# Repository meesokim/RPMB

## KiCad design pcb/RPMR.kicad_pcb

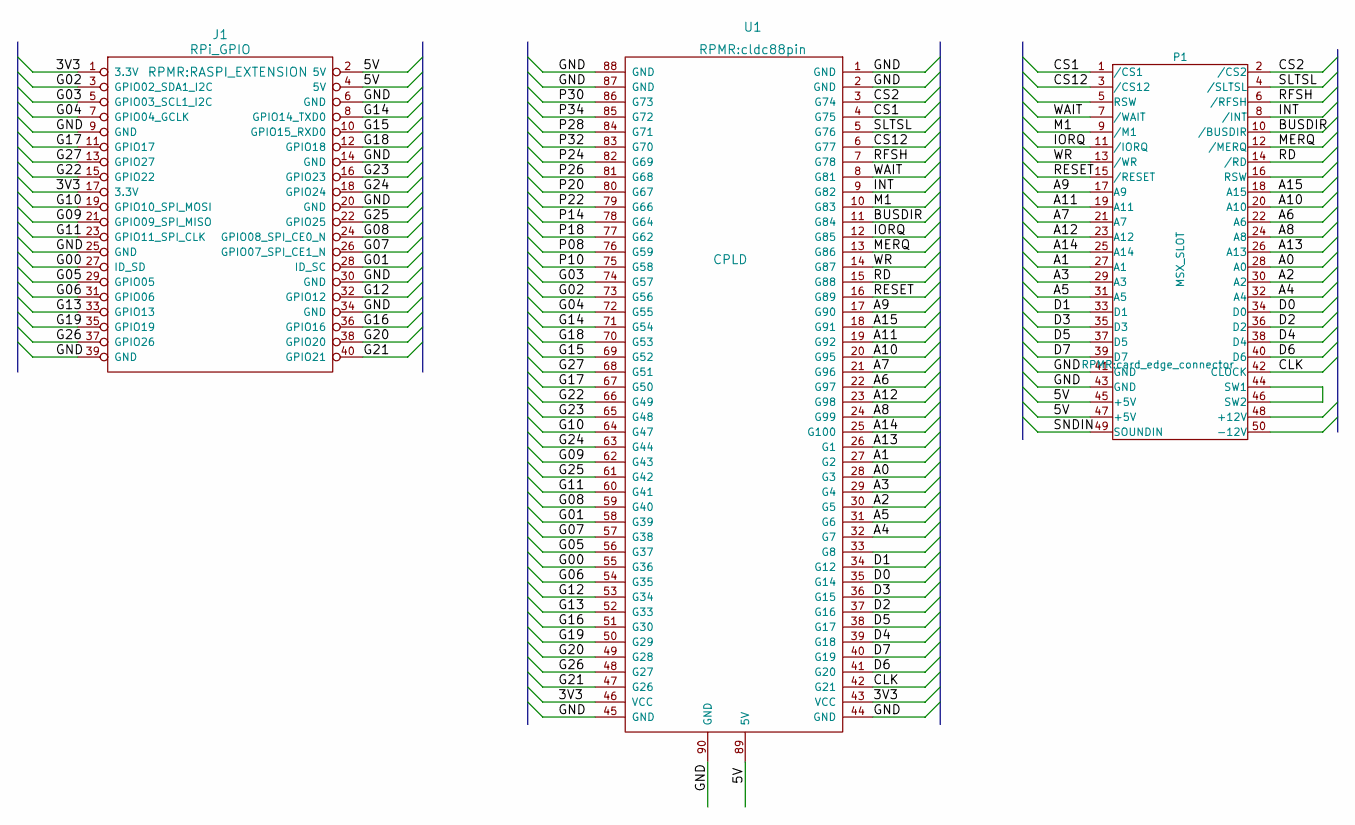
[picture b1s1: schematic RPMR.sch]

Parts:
J1: RPi_GPIO; RASPI_EXTENSION
P1: MSX_SLOT; card_edge_connector
U1: CPLD; cldc88pin

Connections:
/3V3: J1.1 (3.3V), J1.17 (3.3V), U1.43 (VCC), U1.46 (VCC)
/5V: J1.2 (5V), J1.4 (5V), P1.45 (+5V), P1.47 (+5V), U1.89 (5V)
/A0: P1.28 (A0), U1.28 (G3)
/A1: P1.27 (A1), U1.27 (G2)
/A2: P1.30 (A2), U1.30 (G5)
/A3: P1.29 (A3), U1.29 (G4)
/A4: P1.32 (A4), U1.32 (G7)
/A5: P1.31 (A5), U1.31 (G6)
/A6: P1.22 (A6), U1.22 (G97)
/A7: P1.21 (A7), U1.21 (G96)
/A8: P1.24 (A8), U1.24 (G99)
/A9: P1.17 (A9), U1.17 (G90)
/A10: P1.20 (A10), U1.20 (G95)
/A11: P1.19 (A11), U1.19 (G92)
/A12: P1.23 (A12), U1.23 (G98)
/A13: P1.26 (A13), U1.26 (G1)
/A14: P1.25 (A14), U1.25 (G100)
/A15: P1.18 (A15), U1.18 (G91)
/BUSDIR: P1.10 (/BUSDIR), U1.11 (G84)
/CLK: P1.42 (CLOCK), U1.42 (G21)
/CS1: P1.1 (/CS1), U1.4 (G75)
/CS2: P1.2 (/CS2), U1.3 (G74)
/CS12: P1.3 (/CS12), U1.6 (G77)
/D0: P1.34 (D0), U1.35 (G14)
/D1: P1.33 (D1), U1.34 (G12)
/D2: P1.36 (D2), U1.37 (G16)
/D3: P1.35 (D3), U1.36 (G15)
/D4: P1.38 (D4), U1.39 (G18)
/D5: P1.37 (D5), U1.38 (G17)
/D6: P1.40 (D6), U1.41 (G20)
/D7: P1.39 (D7), U1.40 (G19)
/G00: J1.27 (ID_SD), U1.55 (G36)
/G01: J1.28 (ID_SC), U1.58 (G39)
/G02: J1.3 (GPIO02_SDA1_I2C), U1.73 (G56)
/G03: J1.5 (GPIO03_SCL1_I2C), U1.74 (G57)
/G04: J1.7 (GPIO04_GCLK), U1.72 (G55)
/G05: J1.29 (GPIO05), U1.56 (G37)
/G06: J1.31 (GPIO06), U1.54 (G35)
/G07: J1.26 (GPIO07_SPI_CE1_N), U1.57 (G38)
/G08: J1.24 (GPIO08_SPI_CE0_N), U1.59 (G40)
/G09: J1.21 (GPIO09_SPI_MISO), U1.62 (G43)
/G10: J1.19 (GPIO10_SPI_MOSI), U1.64 (G47)
/G11: J1.23 (GPIO11_SPI_CLK), U1.60 (G41)
/G12: J1.32 (GPIO12), U1.53 (G34)
/G13: J1.33 (GPIO13), U1.52 (G33)
/G14: J1.8 (GPIO14_TXD0), U1.71 (G54)
/G15: J1.10 (GPIO15_RXD0), U1.69 (G52)
/G16: J1.36 (GPIO16), U1.51 (G30)
/G17: J1.11 (GPIO17), U1.67 (G50)
/G18: J1.12 (GPIO18), U1.70 (G53)
/G19: J1.35 (GPIO19), U1.50 (G29)
/G20: J1.38 (GPIO20), U1.49 (G28)
/G21: J1.40 (GPIO21), U1.47 (G26)
/G22: J1.15 (GPIO22), U1.66 (G49)
/G23: J1.16 (GPIO23), U1.65 (G48)
/G24: J1.18 (GPIO24), U1.63 (G44)
/G25: J1.22 (GPIO25), U1.61 (G42)
/G26: J1.37 (GPIO26), U1.48 (G27)
/G27: J1.13 (GPIO27), U1.68 (G51)
/GND: J1.6 (GND), J1.9 (GND), J1.14 (GND), J1.20 (GND), J1.25 (GND), J1.30 (GND), J1.34 (GND), J1.39 (GND), P1.41 (GND), P1.43 (GND), U1.1 (GND), U1.2 (GND), U1.44 (GND), U1.45 (GND), U1.87 (GND), U1.88 (GND), U1.90 (GND)
/INT: P1.8 (/INT), U1.9 (G82)
/IORQ: P1.11 (/IORQ), U1.12 (G85)
/M1: P1.9 (/M1), U1.10 (G83)
/MERQ: P1.12 (/MERQ), U1.13 (G86)
/P08: U1.76 (G59)
/P10: U1.75 (G58)
/P14: U1.78 (G64)
/P18: U1.77 (G62)
/P20: U1.80 (G67)
/P22: U1.79 (G66)
/P24: U1.82 (G69)
/P26: U1.81 (G68)
/P28: U1.84 (G71)
/P30: U1.86 (G73)
/P32: U1.83 (G70)
/P34: U1.85 (G72)
/RD: P1.14 (/RD), U1.15 (G88)
/RESET: P1.15 (/RESET), U1.16 (G89)
/RFSH: P1.6 (/RFSH), U1.7 (G78)
/SLTSL: P1.4 (/SLTSL), U1.5 (G76)
/SNDIN: P1.49 (SOUNDIN)
/WAIT: P1.7 (/WAIT), U1.8 (G81)
/WR: P1.13 (/WR), U1.14 (G87)
unnamed: P1.44 (SW1), P1.46 (SW2)

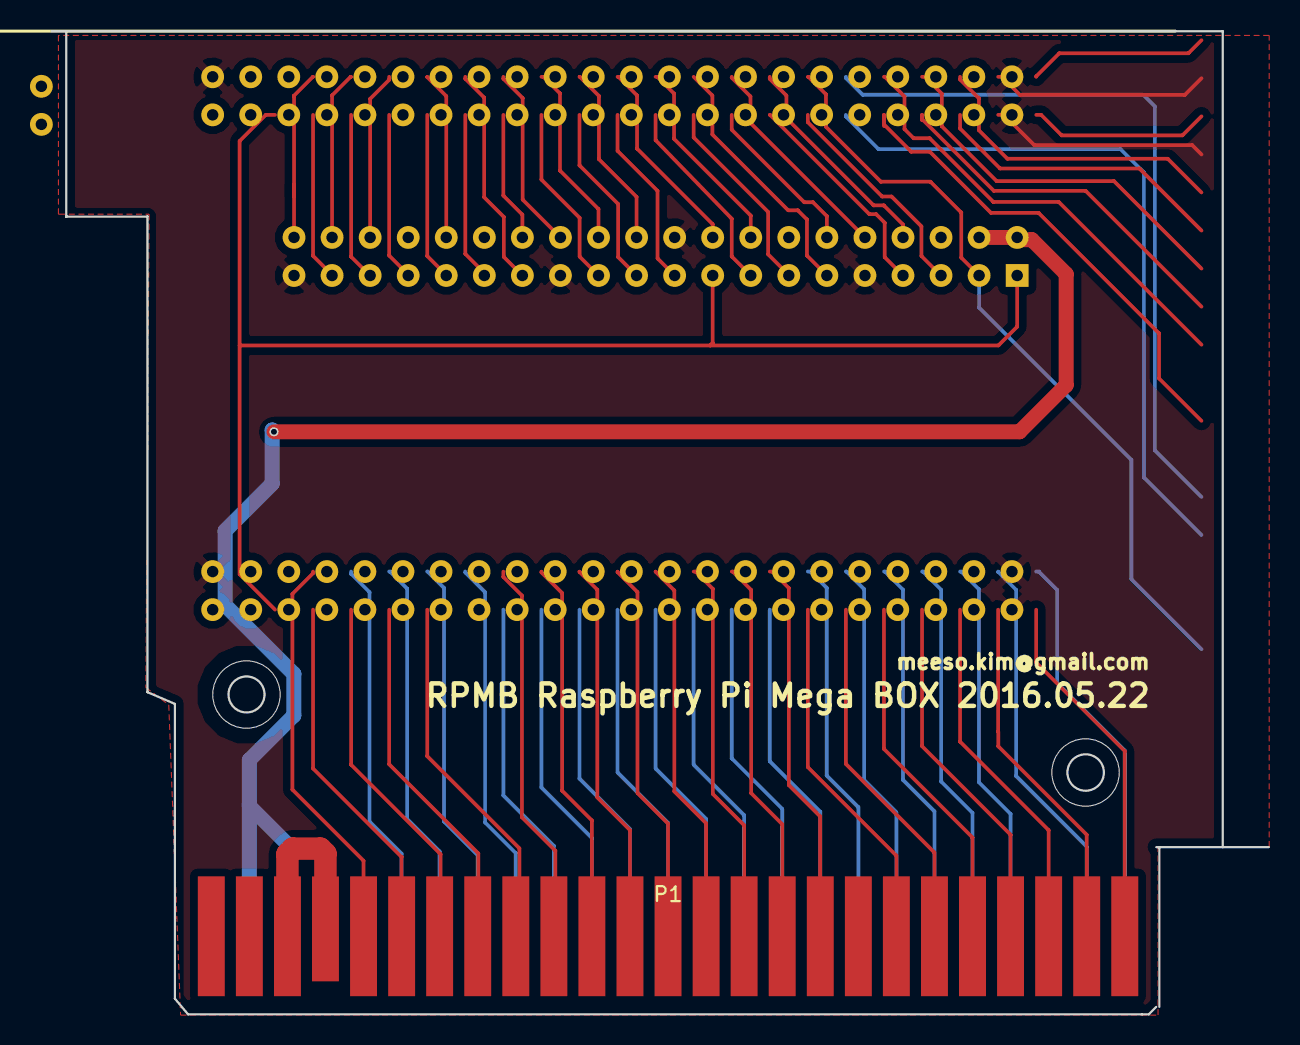
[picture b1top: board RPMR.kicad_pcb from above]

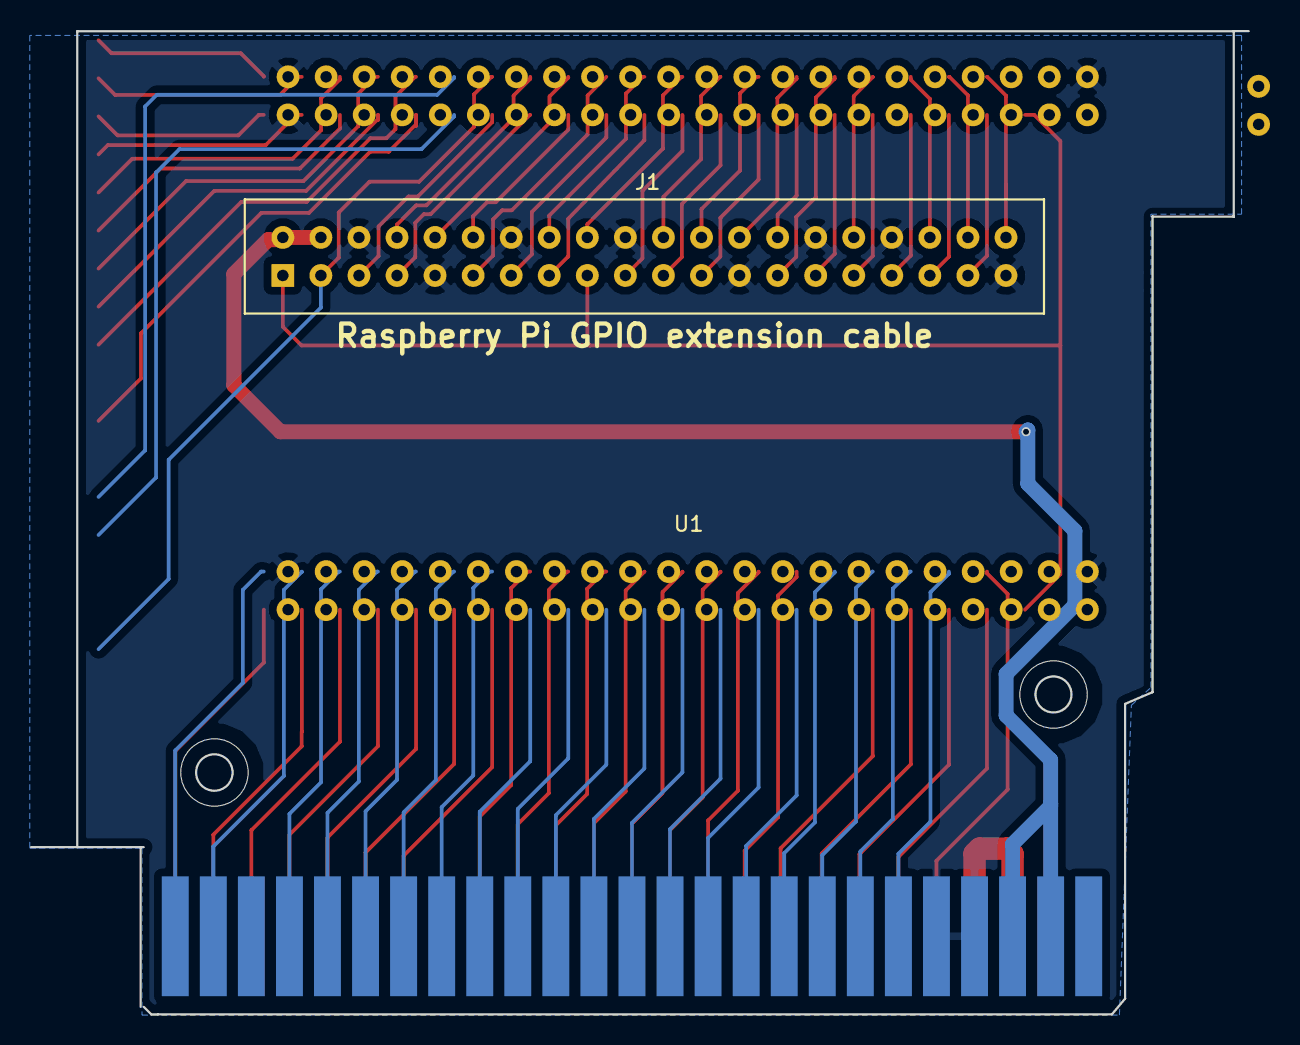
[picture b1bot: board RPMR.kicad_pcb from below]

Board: 2 copper layers, 81.3 x 65.6 mm, 3 parts (2 on the bottom side), 71 nets.

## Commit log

2016-06-14 initial code for RPMB
2016-06-14 RPMR PCB work
2016-06-19 remove refresh pin and small improvement
